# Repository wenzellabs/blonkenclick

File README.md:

# blonkenclick

a blinken clock.

a beginner's solder kit with a fancy RGB 16 segment display (6 digits wide), a realtime clock, a temperature sensor around an ESP32 microprocessor running micropython.

As a display it uses our [digitus16](https://github.com/wenzellabs/digitus16) 16 segment display.

## Parts List

| quantity | symbol | description                 | notes               |
|----------|--------|-----------------------------|---------------------|
|    1     |   -    | PCB                         | the rectangular black blonkenclick PCB |
|    1     |  R1    | LDR                         | light dependent resistor, white ceramic, red wiggly lines |
|    1     |  R2    | 10 kOhm resistor            | we may want to reduce the val once we see a real 5528 |
|    1     |  U2    | RTC module                  | here your time is kept even when unplugged, running from the CR2032 |
|    1     |  U1    | ESP32 C3 super mini         | small processor board with red "C3" labelled antenna and USB-C |
|    1     |   -    | DS18B20 temp sens           | DS18B20 1-wire digital temperature sensor |
|    1     |   -    | digitus16 6 digits          | 6 digits 16-segment RGB display |
|    1     |   -    | CR2032 battery              | for the RTC module  |
| enough   |   -    | pins                        | for mounting all modules and the optional UART header |
|          |        |                             |                     |

# Hardware

## KiCAD schematic board design

you find the design in the [`hardware/`](hardware/) folder. there's also the schematic PDF.

## each pin explained

we want you to learn.

and in turn be creative with your new device.

so that some of your questions you might have get already answered here we describe each pin of the contraption. some are not even used or required for the blonkenclick, we'll still explain them anyway. of course you are free to be creative with your new hardware and modify by soldering more sensors or actors to it, or just change it through it's python software, or run C++ or Rust or Assembly on the device. the hardware comes with WiFi and BT capabilities, but those still lay unused in your blonkenclick.

oh, and there's a maybe useful 4kBytes 24C32 EEPROM on the RTC module at i2c 0x50. store all your encypted secrets here.

| Name    | Source | Sink  | Description/Usage |
| ------- | ------ | ----  | ----------- |
| USB-C   |  sun   | ESP32 | power supply from your PC, powerbank, or PSU. can also be used to upload new firmware or debug |
|   5     | USB-C  | ESP32, EEP, digitus16, DS1307 | main 5V power supply for most sub-components, from USB-C |
|   G     | GND    |      | most electronic circuits have one (lowest) reference voltage/potential called ground. this is it. |
|   3     | ESP32  | LDR voltage divider | for in/external use the ESP32 creates a 3.3V from the main 5V |
|   CK    | ESP32  | digitus16 | SPI clock, often called SCK or CO, here used to control the protocol with the addressable LEDs in digitus16 |
|  Bt     | CR2032 | ESP32 | to keep time without ext power, the RTC needs a battery, here the ESP can monitor the CR2032 bat voltage through one of its ADC channels |
|  NC2    | ESP32  | ESP32 | ESP32's GPIO2, not used in the design (NC=not connected), free for your hacks |
|  QS     | RTC    | ESP32 | the RTC can provide a 1Hz (or 4/8/32kHz) clock, currently unused in SW, but might be interesing for your low power design driven by a 1Hz ISR |
| LDR     | light dep voltage  | ESP32 | LDR5528's voltage divider tells us the ambient light situation through ADC0, we dim the display accordingly |
| Rx      | your PC | ESP32 | optional secondary serial terminal connection to anything, currently unused in SW, but has a nice optional pin header J1 |
| Tx      | ESP32 | your PC | optional secondary serial terminal connection to anything, currently unused in SW, but has a nice optional pin header J1 |
|  DS     | DS18B20 | ESP32 | 1-wire digital thermometer input pin from the DS18B20 sensor, following the onewire protocol |
|  SCL    | ESP32  | RTC/EEP | i2c clock, ESP32 is master |
|  SDA    | ESP32/RTC/EEP | ESP32/RTC/EEP | bidirectional i2c data, ESP32 is master, RTC at 0x68, EEPROM at 0x50 |
|  NC7    |        |       | ESP32's GPIO7, not used in the design (NC=not connected), free for your hacks |
|  DO     | ESP32  | digitus16 | SPI data, often called MOSI or DO, here used to talk the SPI protocol with the addressable LEDs in digitus16 |
|  DI/NC  | ESP32  | ESP32 | ESP32's GPIO5, not used in the design (NC=not connected), free for your hacks |
|         |        |       | |

## Assembly

there's the [assembly guide (english)](doc/en_assembly_guide_blonkenclick.pdf) in the [`doc/`](doc/) folder

TL;DR: assemble the PCB by going through the **Parts List** top to bottom.

## License

licensed under the **CERN Open Hardware Licence Version 2 - Strongly Reciprocal**

see [LICENSE.txt](LICENSE.txt) for details.

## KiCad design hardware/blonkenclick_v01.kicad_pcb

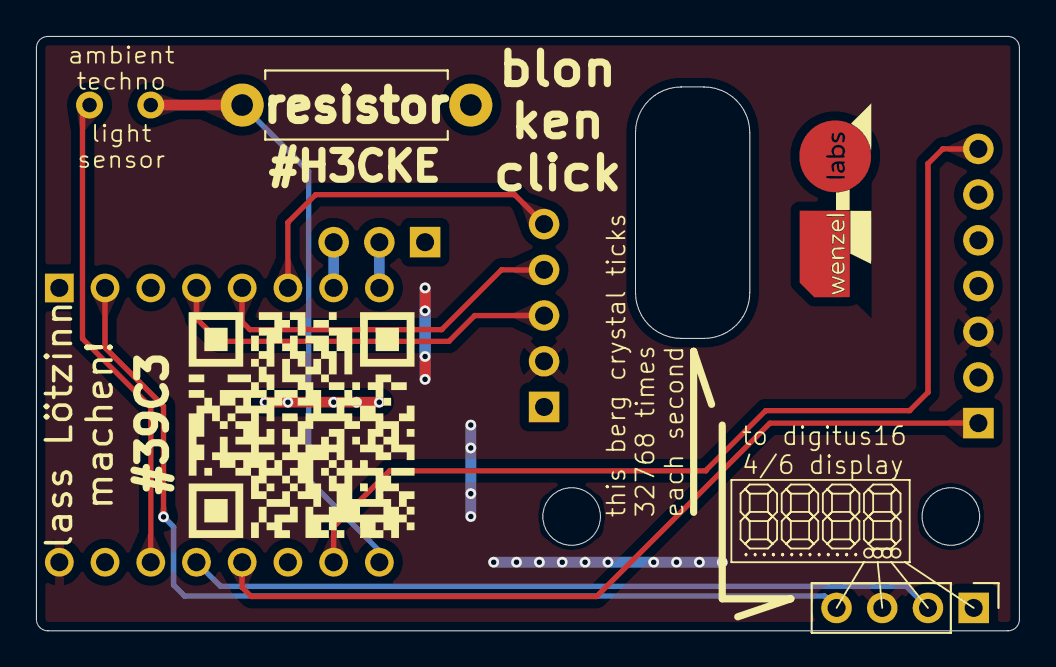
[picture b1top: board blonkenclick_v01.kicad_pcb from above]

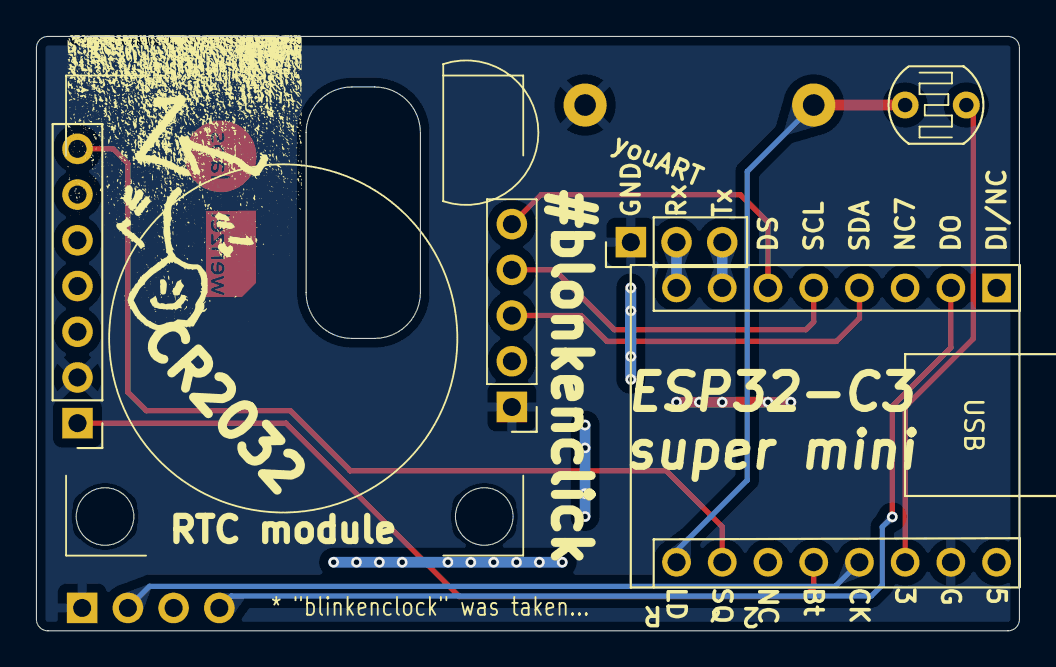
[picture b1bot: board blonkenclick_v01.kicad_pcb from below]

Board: 2 copper layers, 54.6 x 33.0 mm, 7 parts (4 on the bottom side), 13 nets.

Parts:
J1: Conn_01x03; PinHeader_1x03_P2.54mm_Vertical
J2: Conn_01x04; PinHeader_1x04_P2.54mm_Vertical
L1: Logo wenzellabs; wenzellabs_logo_v1_no_silktext_12x4
R1: LDR07; R_LDR_5.1x4.3mm_P3.4mm_Vertical
R2: R; R_Axial_DIN0411_L9.9mm_D3.6mm_P12.70mm_Horizontal
U1: ESP32_C3_Super_Mini
U2: RTC_mod; RTC_module

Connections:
+3.3V: R1.1, U1.-3 (3.3V)
+5V: J2.3, U1.-1 (5V), U2.13 (VCC), U2.22 (VCC)
BAT: U1.3 (GPIO3), U2.11 (BAT)
DS: U1.10 (GPIO10), U2.16 (DS), U2.25 (DS)
GND: J1.1, J2.1, R2.2, U1.-2 (GND), U2.12 (GND), U2.21 (GND)
unnamed: R1.2, R2.1, U1.0 (GPIO0)
RX: J1.2, U1.21 (GPIO21)
SCL: U1.9 (GPIO9), U2.15 (SCL), U2.24 (SCL)
SDA: U1.8 (GPIO8), U2.14 (SDA), U2.23 (SDA)
SPI_CLK: J2.2, U1.4 (GPIO4)
SPI_DO: J2.4, U1.6 (GPIO6)
SQ: U1.1 (GPIO1), U2.17 (SQ)
TX: J1.3, U1.20 (GPIO20)

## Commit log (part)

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2025-12-18 README and .gitattributes
2025-12-18 add all of blonkenclick
2026-01-26 ain't no 4digit digitus16 any more
2026-01-27 list DS18B20 in Parts List
2026-02-21 doc: fix typo, update URLs etc
2026-04-07 update doc
